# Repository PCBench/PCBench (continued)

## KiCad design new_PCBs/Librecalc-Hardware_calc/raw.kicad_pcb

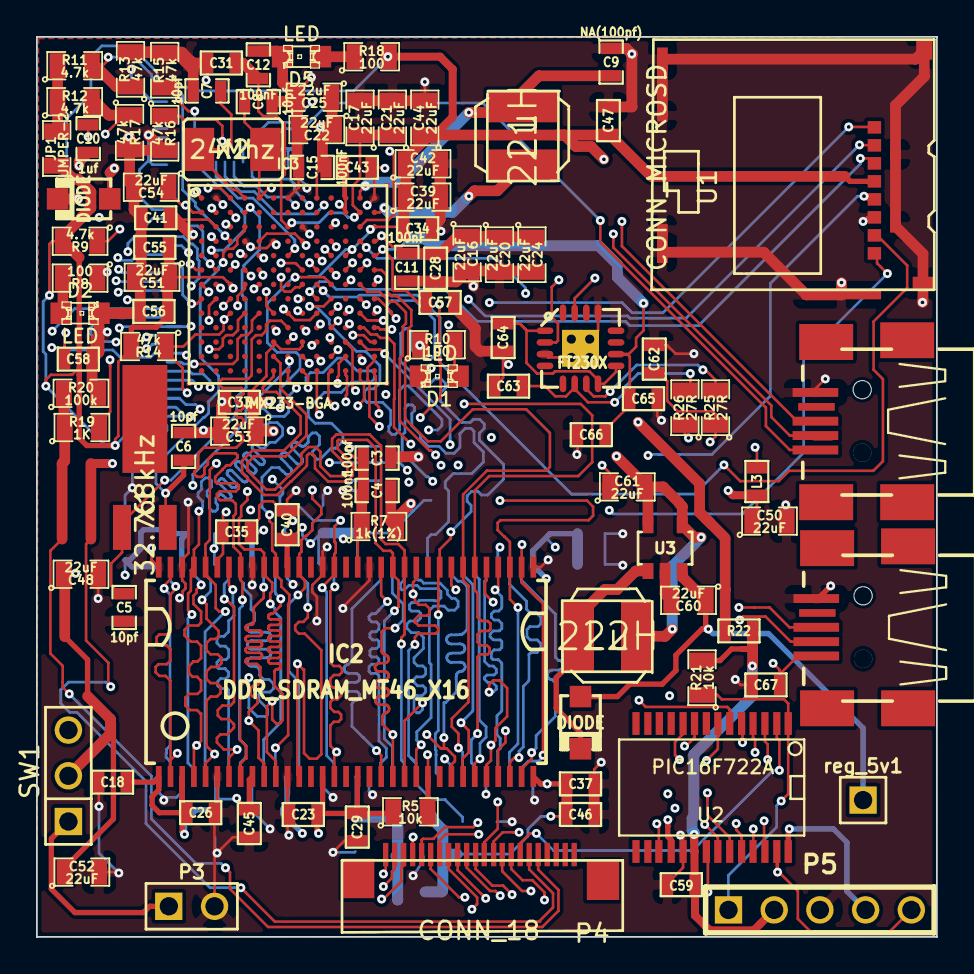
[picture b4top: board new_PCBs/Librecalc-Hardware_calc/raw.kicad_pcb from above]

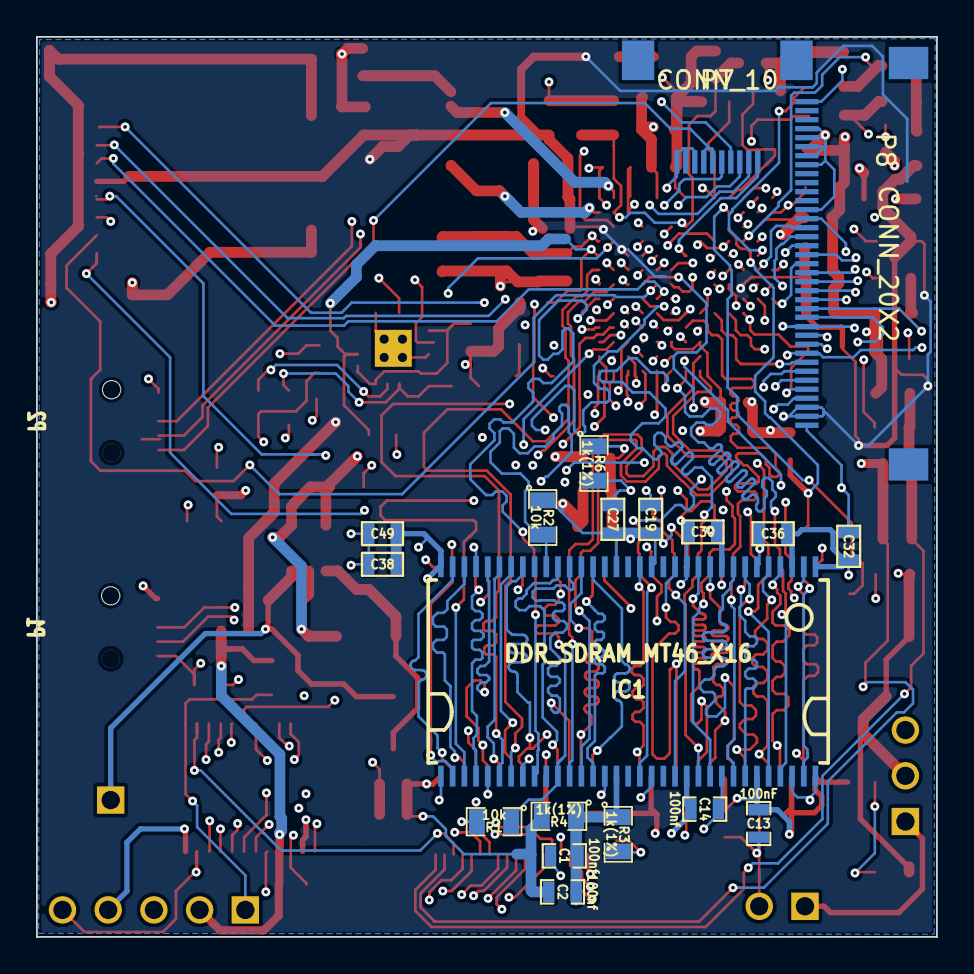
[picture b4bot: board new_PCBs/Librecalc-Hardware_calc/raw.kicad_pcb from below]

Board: 6 copper layers, 50.0 x 50.0 mm, 118 parts (19 on the bottom side), 132 nets.

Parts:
C1, C2, C3, C4, C14: 100nf; SM0603_Capa
C5, C6, C7, C8: 10pf; SM0603_Capa
C9: NA(100pf); SM0603_Capa
C10: 1uf; SM0603_Capa
C11, C12, C13, C15: 100nF; SM0603_Capa
C16, C17, C20, C21, C22, C24, C25, C39, C42, C44, C48, C50, C51, C52, C53, C54, C60, C61: 22uF; SM0805
C18, C23, C27, C30, C32, C36, C38, C41, C59: 100nf; SM0603
C19, C26, C28, C29, C31, C34, C37, C40, C43, C45, C46, C49, C55, C58, C64, C65, C67: 100nF; SM0603
C33, C35, C47, C56, C57, C66: 1uF; SM0603
C62, C63: 47pF; SM0603
D1, D2, D5: LED; LED-0805
D3, D4: DIODE; SOD123
IC1, IC2: DDR_SDRAM_MT46_X16; TSOP66_JEDEC_DDR_SDRAM
IC3: IMX233-BGA; BGA169_0.8mmPitch_11x11mm
JP1: JUMPER-2; SM0805
L1, L2: 22uH; INDUCTOR_BOURNS
L3: ferite; SM0603
P1, P2: CONN_4; CONN_USB_MINI_PIERRE
P3: CONN_2; PIN_ARRAY_2X1
P4: CONN_18; FPC22
P5: CONN_5; PIN_ARRAY_5x1
P7: CONN_10; FPC10
P8: CONN_20X2; FPC37
R1, R2, R5, R21: 10k; SM0805
R3, R4, R6, R7: 1k(1%); SM0805
R8, R10, R18: 100; SM0805
R9, R11, R12: 4.7k; SM0805
R13, R14, R15, R16, R17: 47k; SM0805
R19: 1K; SM0805
R20: 100k; SM0805
R22: 0R; SM0603
R25, R26: 27R; SM0805
SW1: SWITCH_INV; PIN_ARRAY_3X1
U1: CONN_MICROSD; Memory_card_microsd_alps
U2: PIC16F722A; SSOP28
U3: SP6641A; SOT23-5_Opendous
U4: FT230X; QFN16_p0.65mm_MSP430F20xx
X1: 32.768kHz; xtal32.768
X2: 24Mhz; SMDXTAL24mhz
reg_5v1: CONN_1; PIN_ARRAY_1

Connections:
3V3PIC: C59.2, P5.2, R21.2, R22.2, U2.20
5VOUT: P2.1, P7.6, P7.7
5VREG: C60.1, D3.2, U3.3, reg_5v1.1
+2.5V: C2.2, C4.2, C13.1, C14.1, C18.1, C19.1, C23.1, C26.1, C27.1, C29.1, C30.1, C32.1, C33.1, C35.1, C36.1, C37.1, C38.1, C40.1, C45.1, C46.1, C49.1, C53.1, IC1.1, IC1.3, IC1.9, IC1.15, IC1.18, IC1.33, IC1.55, IC1.61, IC2.1, IC2.3, IC2.9, IC2.15, IC2.18, IC2.33, IC2.55, IC2.61, IC3.C10, IC3.L6, IC3.L8, IC3.L10, R2.1, R4.2, R5.1, R7.2
+3.3V: C34.1, C39.1, C42.1, C44.1, C47.1, C51.1, C55.1, C56.1, IC3.C13, IC3.E11, IC3.G3, JP1.1, P8.2, P8.3, R9.2, R14.2, R18.2, R22.1, U1.4
/Processor/SD_CLOCK: IC3.D12, U1.5
/Processor/U_RX: IC3.C3, R9.1, U4.15
/Processor/U_TX: IC3.D2, R8.1, U4.2
DDRA0: IC1.29, IC2.29, IC3.K13
DDRA1: IC1.30, IC2.30, IC3.K12
DDRA2: IC1.31, IC2.31, IC3.J13
DDRA3: IC1.32, IC2.32, IC3.K11
DDRA4: IC1.35, IC2.35, IC3.G10
DDRA5: IC1.36, IC2.36, IC3.G12
DDRA6: IC1.37, IC2.37, IC3.F12
DDRA7: IC1.38, IC2.38, IC3.G11
DDRA8: IC1.39, IC2.39, IC3.G13
DDRA9: IC1.40, IC2.40, IC3.F13
DDRA10: IC1.28, IC2.28, IC3.J12
DDRA11: IC1.41, IC2.41, IC3.H10
DDRA12: IC1.42, IC2.42, IC3.H13
DDR_BA0: IC1.26, IC2.26, IC3.L13
DDR_BA1: IC1.27, IC2.27, IC3.L12
DDR_CAS: IC1.22, IC2.22, IC3.M13
DDR_CE0n: IC2.24, IC3.J10, R5.2
DDR_CE1n: IC1.24, IC3.H12, R2.2
DDR_CKE: IC1.44, IC2.44, IC3.F11, R1.1
DDR_CLK: IC1.45, IC2.45, IC3.M6
DDR_CLKn: IC1.46, IC2.46, IC3.N6
DDR_DO0: IC1.2, IC2.2, IC3.K10
DDR_DO1: IC1.4, IC2.4, IC3.M10
DDR_DO2: IC1.5, IC2.5, IC3.N11
DDR_DO3: IC1.7, IC2.7, IC3.N10
DDR_DO4: IC1.8, IC2.8, IC3.M11
DDR_DO5: IC1.10, IC2.10, IC3.K9
DDR_DO6: IC1.11, IC2.11, IC3.L11
DDR_DO7: IC1.13, IC2.13, IC3.L9
DDR_DO8: IC1.54, IC2.54, IC3.N9
DDR_DO9: IC1.56, IC2.56, IC3.N8
DDR_DO10: IC1.57, IC2.57, IC3.M8
DDR_DO11: IC1.59, IC2.59, IC3.K7
DDR_DO12: IC1.60, IC2.60, IC3.L7
DDR_DO13: IC1.62, IC2.62, IC3.K6
DDR_DO14: IC1.63, IC2.63, IC3.N7
DDR_DO15: IC1.65, IC2.65, IC3.M7
DDR_DQM0: IC1.20, IC2.20, IC3.M12
DDR_DQM1: IC1.47, IC2.47, IC3.M9
DDR_DQS0: IC1.16, IC2.16, IC3.N12
DDR_DQS1: IC1.51, IC2.51, IC3.K8
DDR_RAS: IC1.23, IC2.23, IC3.N13
DDR_WEn: IC1.21, IC2.21, IC3.J11
GND: C1.2, C3.2, C5.1, C6.1, C7.1, C8.1, C9.1, C10.2, C11.2, C12.2, C13.2, C14.2, C15.2, C16.2, C17.2, C18.2, C19.2, C20.2, C21.2, C22.2, C23.2, C24.2, C25.2, C26.2, C27.2, C28.2, C29.2, C30.2, C31.2, C32.2, C33.2, C34.2, C35.2, C36.2, C37.2, C38.2, C39.2, C40.2, C41.2, C42.2, C43.2, C44.2, C45.2, C46.2, C47.2, C48.2, C49.2, C50.2, C51.2, C52.2, C53.2, C54.2, C55.2, C56.2, C57.2, C58.2, C59.1, C60.2, C61.1, C62.2, C63.2, C64.1, C65.2, C66.2, C67.1, D1.2, D2.2, D5.2, IC1.6, IC1.12, IC1.34, IC1.48, IC1.52, IC1.58, IC1.64, IC1.66, IC2.6, IC2.12, IC2.34, IC2.48, IC2.52, IC2.58, IC2.64, IC2.66, IC3.A2, IC3.A7, IC3.A13, IC3.C8, IC3.D4, IC3.D6, IC3.E9, IC3.J7, IC3.J9, P1.4, P2.4, P3.2, P5.3, P7.8, P7.9, P7.10, P8.1, P8.25, P8.30, P8.31, P8.32, P8.33, P8.34, P8.37, R1.2, R3.2, R6.2, R13.2, R15.2, R16.2, R17.2, R20.2, U1.6, U1.9, U2.19, U3.2, U4.3, U4.13, U4.17
KEYBOARD_UART_RX: IC3.J8, U2.18
KEYBOARD_UART_TX: IC3.H8, U2.17
LCD_CS: IC3.F8, P8.4
LCD_D0: IC3.D3, P8.9, R11.2, R13.1
LCD_D1: IC3.E2, P8.10, R15.1
LCD_D2: IC3.E4, P8.11, R16.1
LCD_D3: IC3.F1, P8.12, R12.2, R17.1
LCD_D4: IC3.F3, P8.13
LCD_D5: IC3.F5, P8.14
LCD_D6: IC3.G2, P8.15
LCD_D7: IC3.G5, P8.16
LCD_D8: IC3.H2, P8.17
LCD_D9: IC3.H3, P8.18
LCD_D10: IC3.H1, P8.19
LCD_D11: IC3.G4, P8.20
LCD_D12: IC3.G1, P8.21
LCD_D13: IC3.F4, P8.22
LCD_D14: IC3.F2, P7.5, P8.23
LCD_D15: IC3.E5, P7.3, P8.24
LCD_RD: IC3.G8, P8.7
LCD_RS: IC3.J3, P8.5, R14.1
LCD_RST: IC3.J5, P8.8
LCD_WR: IC3.J4, P8.6
unnamed: C3.1, C4.1, IC2.49, R6.1, R7.1
unnamed: C1.1, C2.1, IC1.49, R3.1, R4.1
unnamed: IC3.D10, R10.1
unnamed: IC3.H9, U1.3
unnamed: IC3.B2, P2.2
unnamed: C62.1, P1.3, R25.1
unnamed: R25.2, U4.7
unnamed: P1.2, R26.1
unnamed: C63.1, R26.2, U4.6
unnamed: C64.2, U4.1, U4.8, U4.9
unnamed: C67.2, L3.1, P1.1
unnamed: JP1.2, R11.1, R12.1
unnamed: C10.1, IC3.A3
unnamed: IC3.B13, L1.1
unnamed: C8.2, IC3.A5, X2.2
unnamed: C9.2, IC3.A12, L1.2
unnamed: C6.2, IC3.C4, X1.1
unnamed: C5.2, IC3.B4, X1.2
unnamed: D2.1, R8.2
unnamed: IC3.A1, P2.3
unnamed: IC3.F10, U1.1
unnamed: IC3.E10, U1.2
unnamed: IC3.G9, U1.7
unnamed: IC3.F9, U1.8
unnamed: C7.2, IC3.A4, X2.1
unnamed: D1.1, R10.2
unnamed: D3.1, L2.1, U3.1
unnamed: P3.1, SW1.1
unnamed: D5.1, R18.1
unnamed: P4.15, U2.3
unnamed: P4.16, U2.2
unnamed: P4.14, U2.4
unnamed: P4.13, U2.5
unnamed: P4.12, U2.6
unnamed: P4.11, U2.7
unnamed: P4.10, U2.10
unnamed: P4.9, U2.9
unnamed: P4.2, P5.5, U2.27
unnamed: P4.5, U2.24
unnamed: P4.4, U2.25
unnamed: P4.3, U2.26
unnamed: P4.1, P5.4, U2.28
unnamed: P4.6, U2.23
unnamed: P5.1, R21.1, U2.1
unnamed: P4.8, U2.21
unnamed: P4.7, U2.22
POWER_5V_IN: C50.1, C57.1, C65.1, C66.1, IC3.E13, L3.2, U4.10
POWER_SWITCH_1: P4.18, R19.1, R20.1
POWER_SWITCH_2: C41.1, IC3.C2, P4.17
PSWITCH: C58.1, IC3.B3, R19.2
SHARP_PWM: IC3.C12, P7.4
SPI_CLK: IC3.E7, P7.1
SPI_CMD: IC3.J6, P7.2
VDD4P2: C15.1, C22.1, C25.1, D4.2, IC3.A9
VDDA: C12.1, C17.1, C21.1, C31.1, IC3.B12, IC3.C7
VDDD: C11.1, C16.1, C20.1, C24.1, C28.1, IC3.D5, IC3.D8, IC3.D13
VDD_BATT: C43.1, C48.1, C52.1, C54.1, C61.2, D4.1, IC3.A11, IC3.B1, IC3.B11, L2.2, SW1.2, U3.4, U3.5

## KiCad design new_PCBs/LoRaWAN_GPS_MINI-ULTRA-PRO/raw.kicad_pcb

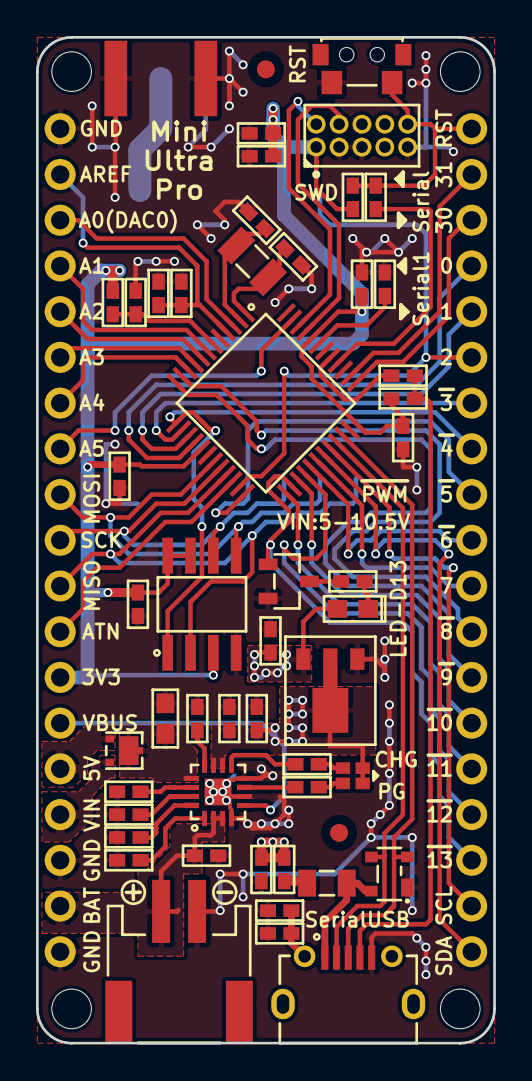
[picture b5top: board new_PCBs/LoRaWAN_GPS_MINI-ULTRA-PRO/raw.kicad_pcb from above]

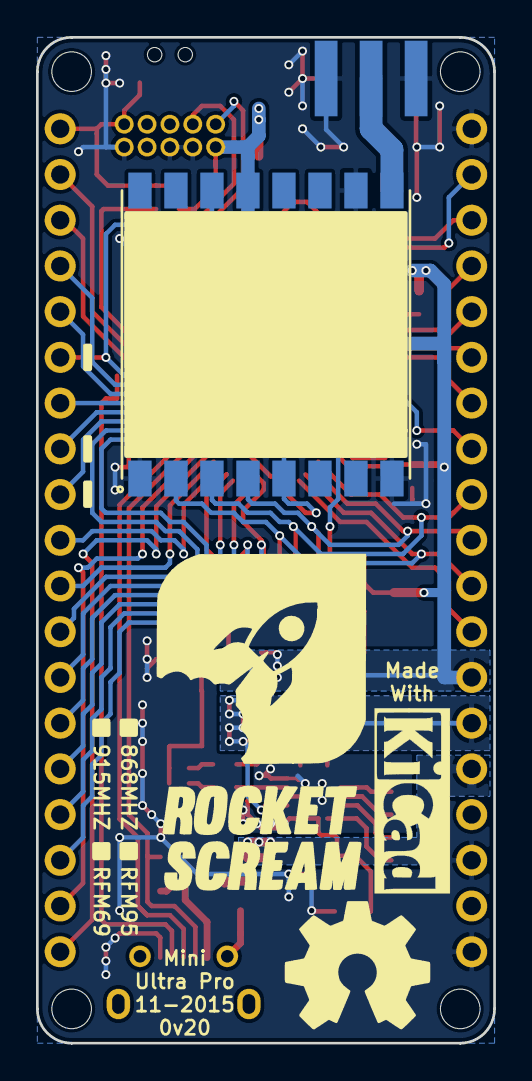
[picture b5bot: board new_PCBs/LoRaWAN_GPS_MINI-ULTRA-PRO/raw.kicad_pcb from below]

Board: 2 copper layers, 25.4 x 55.9 mm, 62 parts (5 on the bottom side), 63 nets.

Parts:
C1, C2: 18pF; CAP-0402
C3, C4, C6, C7, C8, C12, C13: 100nF; CAP-0402
C5, C15, C19: 1uF 10V X5R; CAP-0402
C9: 1uF 50V X5R; CAP-0603
C10, C11, C14, C16, C17: 4.7uF 10V X5R; CAP-0402
C18: 4.7nF 25V X7R; CAP-0402
D1: Orange; LED-0603
D2: LED-DUAL; LED-1615
D3: PRTR5V0U2X; SOT-143B
D4: PMEG3020CPA; SOT-1016
F1: MF-PSMF050X-2; MF-PSMF020X
J1: S2B-PH-SM4-TB
J2: MICRO-USB
J3: RF-SMA-EDGE
J4, J5: CONN-HDR-1x19; HDR_1x19_Pitch2.54mm_WithoutSilk
J6: CONN-HDR-2x5; HDR_2x5_Pitch1.27mm
L1, L2: BKP1005TS121-T; IND-0402
LOGO1: LOGO-ROCKET-SCREAM; LOGO-ROCKET-SCREAM_Vertical_Small
LOGO2: LOGO-OSHW; LOGO-OSHW_Small
LOGO3: LOGO-KICAD; LOGO-KICAD_XSmall
M1, M2, M3, M4: MOUNT_HOLE; HOLE_NPTH_2.2MM
M5, M6: FIDUCIAL; FIDUCIAL-1MM
Q1: 2N7002LT1G; SOT-23
R1, R10, R13: 2K2; RES-0402
R2, R3: 330R; RES-0402
R4, R8, R12: 10K; RES-0402
R5: 1M; RES-0402
R6: 1K18; RES-0402
R7: 46K4; RES-0402
R9: 2K94; RES-0402
R11: 100K; RES-0402
SW1: SPNO; TS-018
U1: ATSAMD21G18A-AU; TQFP-48_7x7mm_Pitch0.5mm
U2: BQ24074RGTT; QFN-16_3x3mm
U3: RFM95W; RFM9xW
U4: MCP1700T-3302E/MB; SOT-89
U5: S25FL116K0XMFI041; SOIC-8-N
Y1: FC-135; ABS07

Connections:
3V3: C3.1, C7.1, C8.1, C11.1, C12.1, C13.1, C19.1, D1.2, J4.13, J6.1, L2.2, R4.1, R11.2, U1.17, U1.36, U1.44, U3.13, U4.3, U5.3, U5.7, U5.8
5V0: C10.1, D4.1, J4.15, L1.1
/A0: J4.3, U1.3
/A1: J4.4, U1.7
/A2: J4.5, U1.8
/A3: J4.6, U1.9
/A4: J4.7, U1.10
/A5: J4.8, U1.47
/ATN: J4.12, U1.22
/CHG: R13.1, U2.9
/D0: J5.4, U1.16
/D1: J5.5, U1.15
/D2: J5.6, U1.23, U3.14
/D3: J5.7, U1.14
/D4: J5.8, U1.13, U5.1
/D5: J5.9, U1.24, U3.5
/D6: J5.10, U1.29
/D7: J5.11, U1.30
/D8: J5.12, U1.11
/D9: J5.13, U1.12
/D10: J5.14, U1.27
/D11: J5.15, U1.25
/D12: J5.16, U1.28
/D13: J5.17, Q1.1, U1.26
/D30: J5.3, U1.37
/D31: J5.2, U1.38
/MISO: J4.11, U1.21, U3.2, U5.2
/MOSI: J4.9, U1.19, U3.3, U5.5
/PG: R12.1, U2.7
/RESET: R2.1, U1.40
/RST: J5.1, J6.10, R2.2, R4.2, SW1.2
/SCK: J4.10, U1.20, U3.4, U5.6
/SCL: J5.18, U1.32
/SDA: J5.19, U1.31
/SWCLK: J6.4, U1.45
/SWDIO: J6.2, U1.46
/USB+: D3.2, J2.3, U1.34
/USB-: D3.3, J2.2, U1.33
/USB_ID: R3.2, U1.41
AREF: C6.1, C14.1, J4.2, U1.4
GND: C1.1, C2.1, C3.2, C4.2, C5.2, C6.2, C7.2, C8.2, C9.1, C10.2, C11.2, C12.2, C13.2, C14.2, C15.2, C16.2, C17.2, C18.2, C19.2, D3.1, J1.2, J2.5, J3.2, J3.3, J3.4, J3.5, J4.1, J4.17, J4.19, J6.3, J6.5, J6.9, Q1.2, R5.2, R6.1, R7.1, R8.2, R9.1, R10.1, SW1.1, U1.5, U1.18, U1.35, U1.42, U2.4, U2.6, U2.8, U2.17, U3.1, U3.8, U3.10, U4.1, U5.4
unnamed: C1.2, U1.2, Y1.1
unnamed: C2.2, U1.1, Y1.2
unnamed: C4.1, L2.1, U1.6
unnamed: C5.1, U1.43
unnamed: C18.1, J2.6, R5.1
unnamed: D1.1, R1.1
unnamed: D2.3, R13.2
unnamed: D2.4, R12.2
unnamed: F1.1, L1.2
unnamed: J2.4, R3.1, R11.1
unnamed: J3.1, U3.9
unnamed: Q1.3, R1.2
unnamed: R6.2, U2.12
unnamed: R7.2, U2.14
unnamed: R8.1, U2.1
unnamed: R9.2, U2.15
unnamed: R10.2, U2.16
VBAT: C16.1, J1.1, J4.18, U2.2, U2.3
VBUS: C15.1, C17.1, D2.1, D2.2, J4.14, U2.5, U2.10, U2.11, U4.2
VEXT: C9.2, D4.3, U2.13
VIN: D4.2, J4.16
VUSB: D3.4, F1.2, J2.1

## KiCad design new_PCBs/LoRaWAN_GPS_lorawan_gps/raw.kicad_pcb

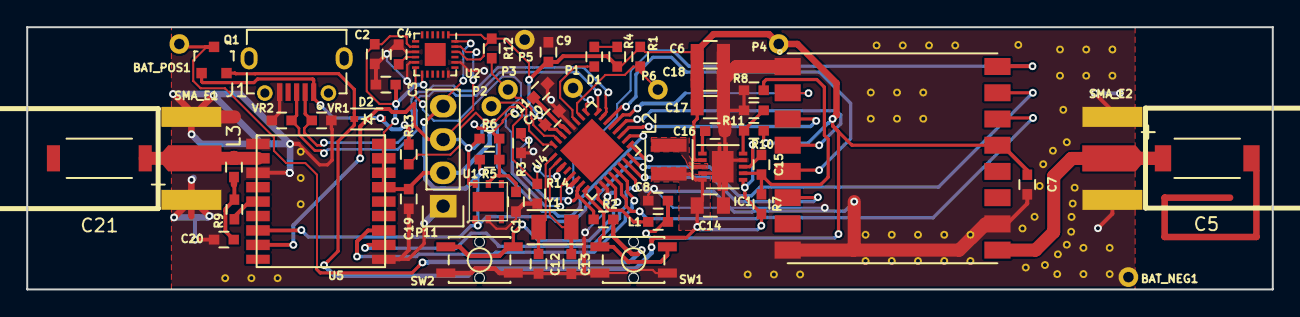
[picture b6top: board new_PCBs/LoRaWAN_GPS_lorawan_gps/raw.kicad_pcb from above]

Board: 2 copper layers, 95.0 x 20.0 mm, 64 parts (0 on the bottom side), 43 nets.

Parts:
BAT_NEG1: CONN_01X01; Measurement_Point_Round-TH_Small
BAT_POS1: CONN_01X01; Measurement_Point_Round-TH_Small
C1, C2, C4, C7, C15, C16, C19: 100nF; C_0603
C3: 10nF; C_0603
C5: CP; 0868AT43A0020
C6, C14, C17, C18: 10uF; C_0805
C8, C10: 100n; C_0603
C9, C11: 1u; C_0603
C12, C13: 22p; C_0603
C20: 33nF; C_0603
C21: CP; 1575AT43A0040
D1: LED; C_0603
D2: D_Schottky; SOD-323
IC1: TPS61201; VSON-10-1(4)EP_3x3mm_Pitch0.5mm
J1: MICRO-USB
L1: 100R; C_0603
L2: 2.2uH; Neosid_Inductor_SMS-ME3015
L3: INDUCTOR_SMALL; C_0603
P1: BL_PAD; Measurement_Point_Round-TH_Small
P2: SWD_DAT; Measurement_Point_Round-TH_Small
P3: SWD_CLK; Measurement_Point_Round-TH_Small
P4: SWD_3V3; Measurement_Point_Round-TH_Small
P5: SWD_GND; Measurement_Point_Round-TH_Small
P6: SWD_RST; Measurement_Point_Round-TH_Small
P11: CONN_01X04; Pin_Header_Straight_1x04
Q1: Q_PMOS_GSD; SOT-23
R1, R2, R12: 10k; C_0603
R3: 2k; C_0603
R4, R5, R6: 1k; C_0603
R7: 2M; C_0603
R8: 220K; C_0603
R9: 10R; C_0603
R10, R11: DNF; C_0603
R13, R14: R; C_0603
SMA_E1, SMA_E2: SMA_EDGE
SW1, SW2: SW_PUSH; TL1014BF180QG
U1: SHT21
U2: MPU-9250; QFN-24-1EP_3x3mm_Pitch0.4mm
U3: RFM9xW
U4: SAMD21E17A; QFN-32-1EP_5x5mm_Pitch0.5mm
U5: MAX-M8
VR1, VR2: CG0603MLC-05E; C_0603
Y1: 32.768kHz; ABS07

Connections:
+3V3: C1.1, C2.1, C3.1, C6.1, C7.1, C8.1, C9.1, C10.1, C17.1, C18.1, C19.1, IC1.2, L1.2, P4.1, P11.2, R1.1, R4.1, R5.1, R6.1, R10.1, R12.2, U1.5, U2.1, U2.8, U2.13, U2.22, U3.13, U4.30, U5.6, U5.7, U5.8, U5.9
/9axis/INT_9AXIS: U2.12, U4.5
/Battery and USB Connector/D+: J1.3, U4.24, VR2.1
/Battery and USB Connector/D-: J1.2, U4.23, VR1.1
/Battery and USB Connector/V_BAT: BAT_POS1.1, Q1.3, R2.1
/Battery and USB Connector/V_USB_Sense: R13.2, R14.1, U4.3
/GPS/GPS_FEEDER: C21.1, L3.2, SMA_E1.1, U5.11
/MCU/#RESET: P6.1, R1.2, U4.26
/MCU/AIN_6: R2.2, R3.1, U4.7
/MCU/MPU_D14: U3.6, U4.15
/MCU/MPU_IN14: U3.15, U4.16
/MCU/MPU_INT5: U3.16, U4.6
/MCU/MPU_INT9: U3.14, U4.12
/MCU/MPU_MISO: U3.2, U4.21
/MCU/MPU_MOSI: U3.3, U4.19
/MCU/MPU_RX1: U4.14, U5.2
/MCU/MPU_SCK: U3.4, U4.20
/MCU/MPU_SCL: P11.3, R6.2, U1.6, U2.23, U4.18, U5.17
/MCU/MPU_SDA: P11.4, R5.2, U1.1, U2.24, U4.17, U5.16
/MCU/MPU_SS: U3.5, U4.22
/MCU/MPU_TX1: U4.13, U5.3
GND: BAT_NEG1.1, C1.2, C2.2, C3.2, C4.2, C6.2, C7.2, C8.2, C9.2, C10.2, C11.2, C12.2, C13.1, C14.2, C16.2, C17.2, C18.2, C19.2, C20.2, IC1.4, IC1.9, IC1.11, IC1.12, IC1.13, IC1.14, IC1.15, J1.5, P5.1, P11.1, R3.2, R8.2, R11.2, R14.2, SMA_E1.0, SMA_E1.2, SMA_E1.3, SMA_E1.4, SMA_E2.0, SMA_E2.2, SMA_E2.3, SMA_E2.4, SW1.2, SW2.2, U1.2, U2.9, U2.11, U2.18, U2.20, U3.1, U3.8, U3.10, U4.10, U4.28, U5.1, U5.10, U5.12, VR1.2, VR2.2
unnamed: C4.1, U2.10
unnamed: C5.1, SMA_E2.1, U3.9
unnamed: C11.1, U4.29
unnamed: C12.1, U4.1, Y1.2
unnamed: C13.2, U4.2, Y1.1
unnamed: C14.1, C15.1, D2.1, IC1.5, IC1.6, IC1.8, L2.1, Q1.2, R7.1
unnamed: C15.2, IC1.7, R7.2, R8.1
unnamed: C16.1, IC1.1
unnamed: C20.1, L3.1, R9.1
unnamed: D1.1, U4.27
unnamed: D1.2, R4.2
unnamed: D2.2, J1.1, Q1.1, R13.1
unnamed: IC1.3, L2.2
unnamed: IC1.10, R10.2, R11.1
unnamed: L1.1, U4.9
unnamed: P1.1, U4.25
unnamed: P2.1, U4.32
unnamed: P3.1, R12.1, U4.31
unnamed: R9.2, U5.14
unnamed: SW1.1, U4.8
unnamed: SW2.1, U4.11

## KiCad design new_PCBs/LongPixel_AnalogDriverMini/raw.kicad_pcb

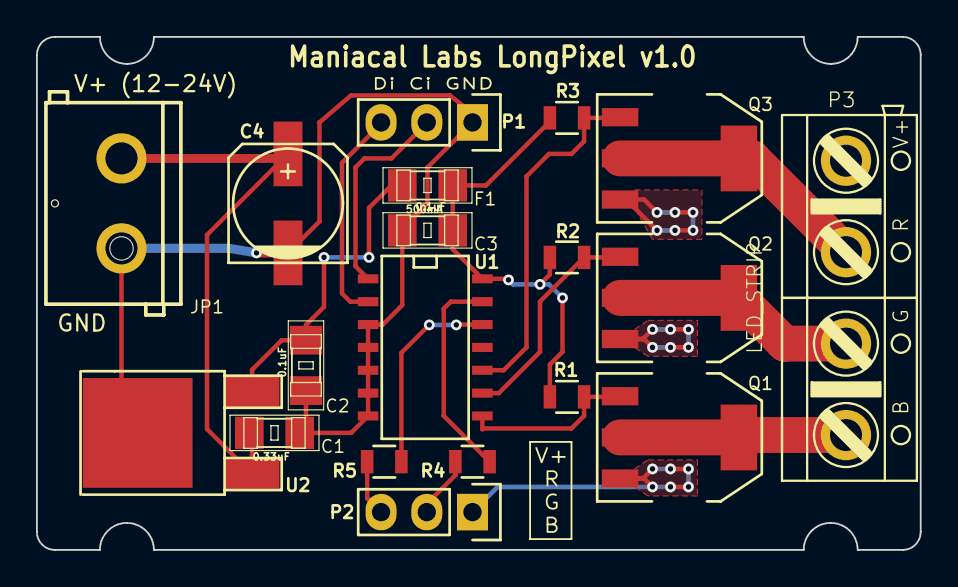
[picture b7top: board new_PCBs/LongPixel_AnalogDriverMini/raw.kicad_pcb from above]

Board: 2 copper layers, 49.1 x 28.5 mm, 19 parts (0 on the bottom side), 16 nets.

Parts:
C1: 0.33uF; ML_SparkFun-1206
C2, C3: 0.1uF; ML_SparkFun-1206
C4: CP; c_elec_6.3x5.3
F1: 500mA; ML_SparkFun-1206
JP1: 12V_IN; ML_SparkFun-SCREWTERMINAL-5MM-2
P1: GNDCLKDATA_IN; Pin_Header_Straight_1x03
P2: GNDCLKDATA_OUT; Pin_Header_Straight_1x03
P3: LED_STRIP; AB2_TB_04_RA_5.08MM_L-BLU
Q1, Q2, Q3: Q_NMOS_GDSD FDT457N SOT-223; SOT-223
R1, R2, R3: 10K; R_0805
R4, R5: 50; R_0805
U1: WS2801; SOIC-14_N
U2: L78M05CDT-TR; ML_DPAK-2

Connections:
5V: C3.1, F1.2, R1.1, R2.1, R3.1, U1.14
12V: C1.1, C4.1, JP1.2, P3.1, U2.VI
+5V: C2.1, F1.1, U2.VO
CKI: P1.2, U1.1
CKO: R4.1, U1.13
GND: C1.2, C2.2, C3.2, C4.2, JP1.1, P1.1, P2.1, Q1.3, Q2.3, Q3.3, U1.3, U1.4, U1.5, U1.6, U1.7, U2.GND
unnamed: P2.2, R4.2
unnamed: P2.3, R5.2
unnamed: P3.2, Q3.2, Q3.4
unnamed: P3.3, Q2.2, Q2.4
unnamed: P3.4, Q1.2, Q1.4
unnamed: Q1.1, R1.2, U1.8
unnamed: Q2.1, R2.2, U1.9
unnamed: Q3.1, R3.2, U1.10
SDI: P1.3, U1.2
SDO: R5.1, U1.12

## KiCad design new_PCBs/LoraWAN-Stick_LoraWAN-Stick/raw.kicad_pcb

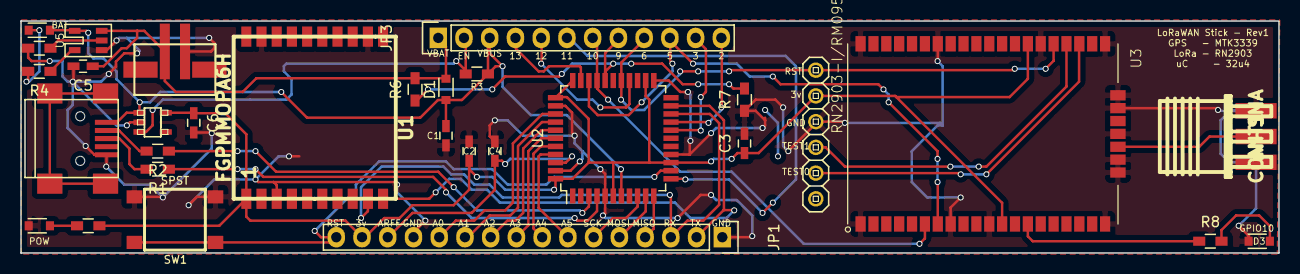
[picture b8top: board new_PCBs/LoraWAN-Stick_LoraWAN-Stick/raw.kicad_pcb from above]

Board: 2 copper layers, 124.2 x 22.9 mm, 31 parts (0 on the bottom side), 40 nets.

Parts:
ANT1: CON-SMA; CON-SMA-EDGE
C1, C2, C5, C6: 10uF; C_0603_HandSoldering
C3, C4: 1uF; C_0603_HandSoldering
CN1: JST_2PIN-SMT; adafruit-JST-PH-2-SMT
D1: DIODESCH; D_0805
D2: LED-BAT; D_0805
D3: LED-RED; D_0805
D4: LED-POW; D_0805
JP1: CONN_01X16; Pin_Header_Straight_1x16
JP2: PINHD-1X6; adafruit-1X06
JP3: PINHD-1X12; Pin_Header_Straight_1x12
P1: USB_OTG; USB_Mini-B
R1, R2: 22; R_0603_HandSoldering
R3, R6, R7: 100k; R_0603_HandSoldering
R4, R8, R9: 1k; R_0603_HandSoldering
R5: 10k; R_0603_HandSoldering
SW1: SPST; SW_PUSH_SMD
U1: FGPMMOPA6H
U2: ATmega32U4-AU; TQFP-44_10x10mm_Pitch0.8mm
U3: RN2903-I/RM095; XCVR_RN2903-I%2fRM095
U4: SPX3819
U5: MCP73831

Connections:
3v3: C2.1, C3.1, C6.1, JP1.15, JP2.2, R9.1, U1.1, U2.6, U2.14, U2.24, U2.33, U2.34, U2.44, U3.12, U3.34, U4.4
9: JP3.8, R6.1, R7.2, U2.29
/0: JP1.3, U1.9, U2.20
/1: JP1.2, U1.10, U2.21
/2: JP3.12, U2.19
/3: JP3.11, U2.18
/5: JP3.10, U2.31, U3.7
/6: JP2.1, JP3.9, U2.27, U3.32
/10: JP3.7, U2.30, U3.6
/11: JP3.6, U2.12
/12: JP3.5, U2.26
/13: JP3.4, U2.32
/A0: JP1.12, U2.36
/A1: JP1.11, U2.37
/A2: JP1.10, U2.38
/A3: JP1.9, U2.39
/A4: JP1.8, U2.40
/A5: JP1.7, U2.41
/EN: JP3.2, R3.1, U4.3
/MISO: JP1.4, U2.11
/MOSI: JP1.5, U2.10
/SCK: JP1.6, U2.9
/TEST0: JP2.5, U3.30
/TEST1: JP2.4, U3.31
ARFF: C4.1, JP1.14, U2.42
GND: ANT1.2, ANT1.3, ANT1.4, ANT1.5, C1.2, C2.2, C3.2, C4.2, C5.2, C6.2, CN1.1, D3.1, D4.1, JP1.1, JP1.13, JP2.3, P1.5, R5.1, R7.1, SW1.2, U1.3, U1.12, U1.19, U2.5, U2.15, U2.23, U2.35, U2.43, U3.1, U3.8, U3.11, U3.20, U3.21, U3.22, U3.24, U3.26, U3.27, U3.28, U3.33, U3.41, U3.47, U4.2, U5.2
unnamed: ANT1.1, U3.23
unnamed: D2.1, R4.2
unnamed: D3.2, R8.2
unnamed: D4.2, R9.2
unnamed: P1.2, R2.2
unnamed: P1.3, R1.2
unnamed: R1.1, U2.4
unnamed: R2.1, U2.3
unnamed: R4.1, U5.1
unnamed: R5.2, U5.5
unnamed: R8.1, U3.14
RST: JP1.16, SW1.1, U2.13
VBAT: C5.1, CN1.2, D1.1, JP3.1, R6.2, U5.3
VBUS: C1.1, D1.2, D2.2, JP3.3, P1.1, R3.2, U2.7, U4.1, U5.4
